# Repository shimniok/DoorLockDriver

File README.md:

Circuit for improving door lock performance on old cars. Switches get corroded,
wasting power. Instead, switches drive this MOSFET H-Bridge to deliver nearly
full power to the door lock motors.

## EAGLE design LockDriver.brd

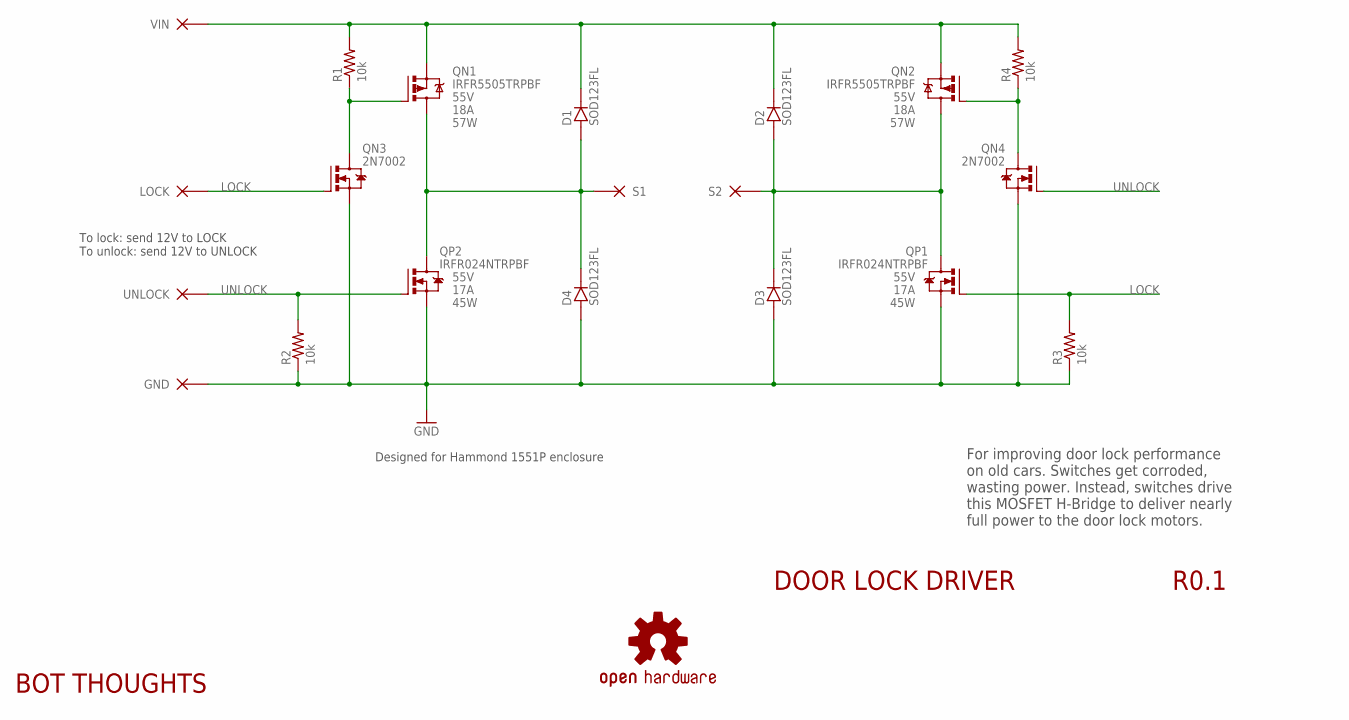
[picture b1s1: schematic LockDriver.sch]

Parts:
D1, D2, D3, D4: SOD123FL
LOGO1: OSHW-LOGOS; OSHW-LOGO-S
QN1, QN2: IRFR5505TRPBF; TO252; VOLTAGE 55V
QN3, QN4: 2N7002; SOT-23
QP1, QP2: IRFR024NTRPBF; TO252; VOLTAGE 55V
R1, R2, R3, R4: 10k; R0603
U$2: BOT-THOUGHTSLOGO_M; BTLOGOM
X1: S1; PAD_14GA
X2: S2; PAD_14GA
X3: VIN; PAD_12GA
X4: GND; PAD_12GA
X5: LOCK; PAD_18GA
X6: UNLOCK; PAD_18GA

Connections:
12V: D1.C, D2.C, QN1.2 (S), QN2.2 (S), R1.2, R4.2, X3.P$1
GND: D3.A, D4.A, QN3.2 (S), QN4.2 (S), QP1.2 (S), QP2.2 (S), R2.1, R3.1, X4.P$1
LOCK: QN3.1 (G), QP1.1 (G), R3.2, X5.P$1
M1: D1.A, D4.C, QN1.3 (D), QP2.3 (D), X1.P$1
M2: D2.A, D3.C, QN2.3 (D), QP1.3 (D), X2.P$1
unnamed: QN1.1 (G), QN3.3 (D), R1.1
unnamed: QN2.1 (G), QN4.3 (D), R4.1
UNLOCK: QN4.1 (G), QP2.1 (G), R2.2, X6.P$1

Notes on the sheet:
DOOR LOCK DRIVER
R0.1
For improving door lock performance on old cars. Switches get corroded, wasting power. Instead, switches drive this MOSFET H-Bridge to deliver nearly full power to the door lock motors.
Designed for Hammond 1551P enclosure
To lock: send 12V to LOCK To unlock: send 12V to UNLOCK

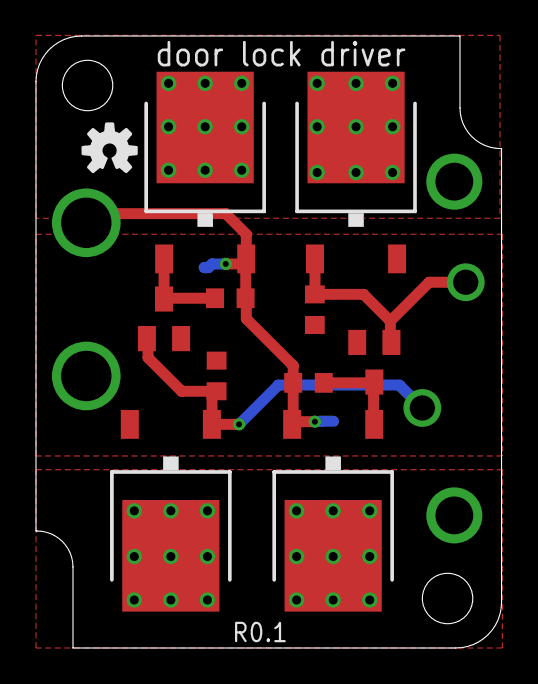
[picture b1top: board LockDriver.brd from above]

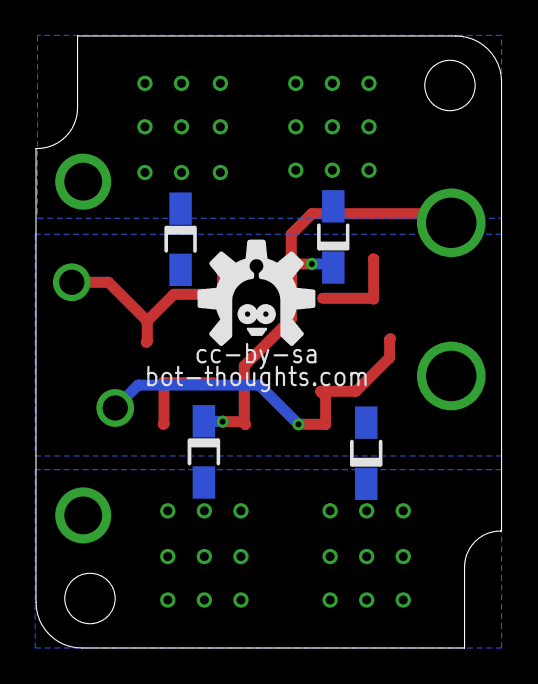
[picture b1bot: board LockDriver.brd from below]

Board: 2 copper layers, 25.9 x 34.0 mm, 23 parts (5 on the bottom side), 8 nets.

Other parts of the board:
U$1: HAMMOND1551P

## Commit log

2015-06-29 initial revision
2017-03-23 added diodes, changed wirepad sizes, layout changes
2017-03-23 added gerbers
2017-03-23 added zip

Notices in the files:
LockDriver.brd:
cc-by-sa
parts and their libraries:
SparkFun-Aesthetics: Licensing: Creative Commons ShareAlike 4.0 International - https://creativecommons.org/licenses/by-sa/4.0
